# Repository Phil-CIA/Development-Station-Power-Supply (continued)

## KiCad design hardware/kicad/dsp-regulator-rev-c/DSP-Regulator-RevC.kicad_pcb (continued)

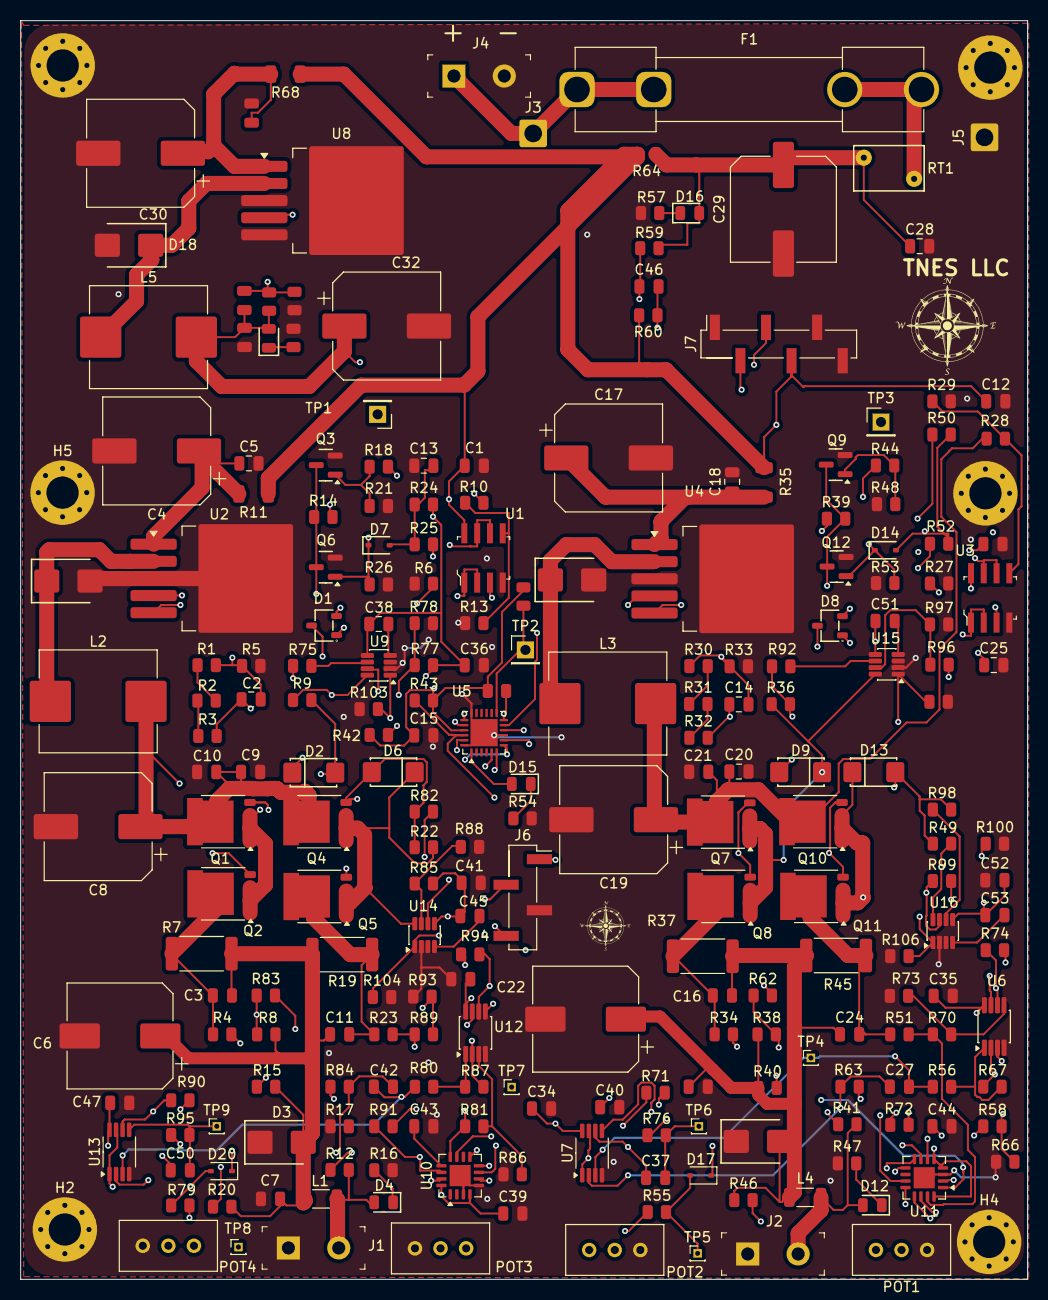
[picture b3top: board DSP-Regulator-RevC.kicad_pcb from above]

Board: 4 copper layers, 100.0 x 125.0 mm, 243 parts (1 on the bottom side), 124 nets.

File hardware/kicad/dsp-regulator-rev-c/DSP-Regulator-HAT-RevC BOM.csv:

"Reference","Qty","Value","LCSC","Manufacturer","Part"
"5mm1","1","","","",""
"10mm1,10mm2","2","","","",""
"C1,C3,C9,C11,C12,C15,C16,C24,C31,C33,C34,C35,C36,C39,C40,C41,C43,C44,C45,C46,C47,C48,C49,C51,C52,C53","26","100nF","C28233,C49678","Samsung Electro-Mechanics,YAGEO","CC0805KRX7R9BB104,CL21B104KCFNNNE"
"C2,C14","2","100pF","C1790","Samsung Electro-Mechanics","CL21C101JBANNNC"
"C4,C30","2","470uf 25V","C48615124","",""
"C5,C18,C20,C38","4","100nF","C28233,C49678","Samsung Electro-Mechanics,YAGEO","CC0805KRX7R9BB104,CL21B104KCFNNNE"
"C6,C22","2","470uf","C48615124","","JVE25V470M10X10"
"C7,C10,C21,C23","4","10uF","C440198","Murata Electronics","GRM21BR61H106KE43L"
"C8,C19,C32","3","330uF 25v","C72510","",""
"C13,C25","2","1nF","C46653","Samsung Electro-Mechanics","CL21B102KBCNNNC"
"C17","1","470uf 50v","C34642","",""
"C26","1","100pF","C1790","Samsung Electro-Mechanics","CL21C101JBANNNC"
"C27,C37,C42,C50","4","1nF","C46653","Samsung Electro-Mechanics","CL21B102KBCNNNC"
"C28","1","100nf","C28233","Samsung Electro-Mechanics","CL21B104KCFNNNE"
"C29","1","1000uf 25v","C401766","","EEEFT1E102UP"
"D1,D8","2","BAT54C,215","C37704","Nexperia","BAT54C,215"
"D2,D6,D9,D13","4","1SMA4742A","C19077480","hongjiacheng","1SMA4742A"
"D3,D11","2","SMBJ6.0CA","C19077561","hongjiacheng","SMBJ6.0CA"
"D4,D12","2","Green","C2297","Hubei KENTO Elec","KT-0805G"
"D5,D10,D18","3","SS54B","C18199181","hongjiacheng","SS54B"
"D7,D14","2","1N5819WS","C191023","Guangdong Hottech","1N5819WS"
"D15,D19","2","Yellow","C2296","Hubei KENTO Elec","KT-0805Y"
"D16","1","Red","C84256","Foshan NationStar Optoelectronics","NCD0805R1"
"D17,D20","2","1N5819WS","C191023","",""
"F1","1","MDL 5","","",""
"J1,J2,J4","3","1935161","","Phoenix Contact",""
"J6","1","1x4 pin 2.54  SMT right","C41417361","",""
"J7","1","1x6 PinHeader","C41417363","",""
"L1,L4","2","L_Ferrite","C85841","",""
"L2,L3,L5","3","33uh","C149598","",""
"POT1,POT2,POT3,POT4","4","3296W-1-103LF","C49190453","Bourns Inc.",""
"Q1,Q2,Q4,Q5,Q7,Q8,Q10,Q11","8","PSMN5R2-60YL","TBD","Nexperia","PSMN5R2-60YLX"
"Q3,Q6,Q9,Q12","4","BSS138","C7420339","hongjiacheng","BSS138"
"R1,R10,R18,R25,R44,R52","6","100Ω","C17408","UNI-ROYAL(Uniroyal Elec)","0805W8F1000T5E"
"R2,R5,R28,R33,R56,R57,R76,R80,R95","9","1kΩ","C17513","UNI-ROYAL(Uniroyal Elec)","0805W8F1001T5E"
"R3","1","1.8kΩ","C17398","UNI-ROYAL(Uniroyal Elec)","0805W8F1801T5E"
"R4,R8,R12,R20,R23,R34,R38,R41,R46,R51,R59,R60,R75,R82,R92,R98","16","10Ω","C17415","UNI-ROYAL(Uniroyal Elec)","0805W8F100JT5E"
"R6,R9,R21,R22,R26,R27,R36,R48,R49,R53,R55,R78,R79,R88,R97,R100","16","100kΩ","C149504","UNI-ROYAL(Uniroyal Elec)","0805W8F1003T5E"
"R7","1","20mΩ","C49164694","",""
"R11,R35,R68","3","0Ω","C17888","UNI-ROYAL(Uniroyal Elec)","1206W4F0000T5E"
"R13,R29","2","33kΩ","C17633","UNI-ROYAL(Uniroyal Elec)","0805W8F3302T5E"
"R14,R39,R42,R43,R58,R62,R63,R70,R71,R72,R81,R83,R84,R89,R90,R91,R101,R102,R103,R104,R105,R106","22","10kΩ","C17414","UNI-ROYAL(Uniroyal Elec)","0805W8F1002T5E"
"R15,R17,R40","3","10Ω","C17415","UNI-ROYAL(Uniroyal Elec)","0805W8F100JT5E"
"R16,R47,R54","3","270Ω","C17590","UNI-ROYAL(Uniroyal Elec)","0805W8F2700T5E"
"R19","1","200mΩ","C7420022","",""
"R24,R50","2","47kΩ","C17713","UNI-ROYAL(Uniroyal Elec)","0805W8F4702T5E"
"R30,R69","2","680Ω","C17798","UNI-ROYAL(Uniroyal Elec)","0805W8F6800T5E"
"R31","1","820Ω","C17837","UNI-ROYAL(Uniroyal Elec)","0805W8F8200T5E"
"R32","1","0Ω","C17477","UNI-ROYAL(Uniroyal Elec)","0805W8F0000T5E"
"R37","1","20m ohms","C49164694","",""
"R45","1","200m ohms","C7420022","",""
"R61","1","3100","C2767486","UNI-ROYAL(Uniroyal Elec)","0805W8F1000T5E"
"R64","1","10mohm","C17477","UNI-ROYAL(Uniroyal Elec)","0805W8F0000T5E"
"R65","1","1k","C17513","UNI-ROYAL(Uniroyal Elec)","0805W8F1001T5E"
"R66,R67,R73,R74,R86,R87,R93,R94","8","510kΩ","C17733","UNI-ROYAL(Uniroyal Elec)","0805W8F5103T5E"
"R77,R85,R96,R99","4","390kΩ","C17656","UNI-ROYAL(Uniroyal Elec)","0805W8F3903T5E"
"RT1","1","5 ohms - 4.5amp","","",""
"TP1,TP2,TP3","3","TestPoint_Small","","",""
"TP4,TP5,TP6,TP7,TP8,TP9","6","TestPoint_Small","","",""
"U1,U3","2","TLV9352","C4366962","Texas Instruments",""
"U2,U4,U8","3","LM2596S-ADJ","C347423","",""
"U5","1","AW9523B","C148077","",""
"U6,U12","2","INA2180A2IDGKR","C2058508","",""
"U7,U13","2","TLV1702AIDGKR","C2870937","",""
"U9,U14,U15,U16","4","LM74502DDFR","C3236215","",""
"U10,U11","2","INA3221","C181255","",""

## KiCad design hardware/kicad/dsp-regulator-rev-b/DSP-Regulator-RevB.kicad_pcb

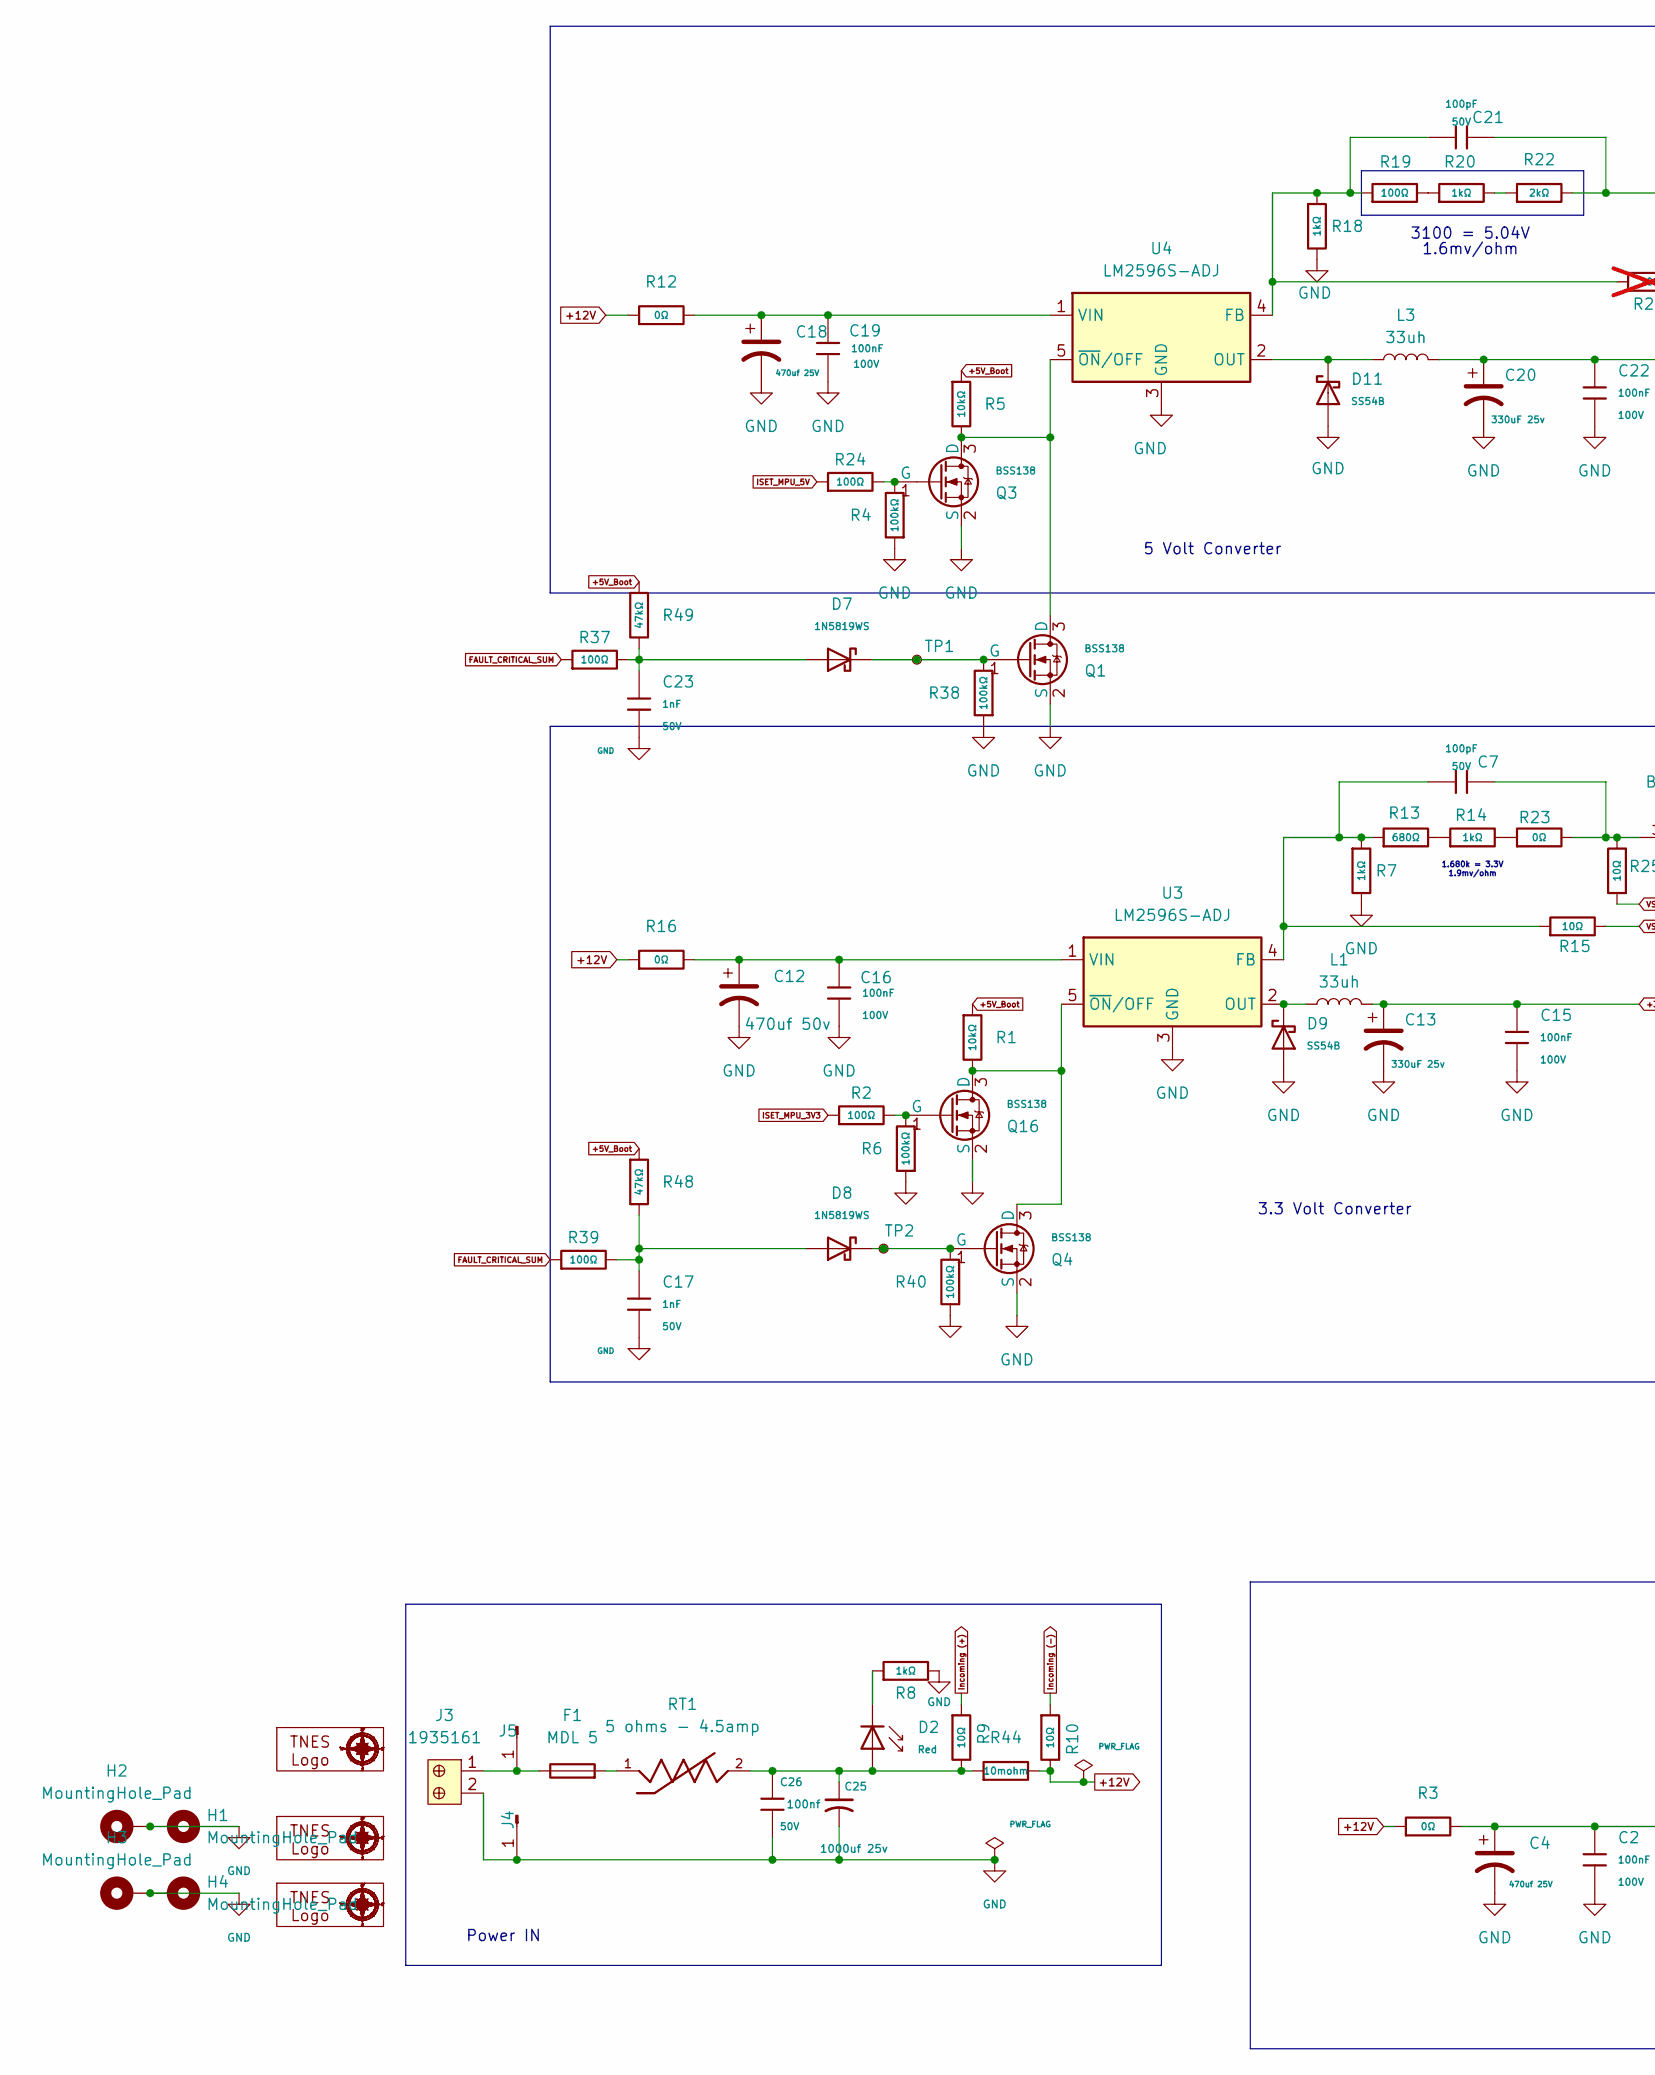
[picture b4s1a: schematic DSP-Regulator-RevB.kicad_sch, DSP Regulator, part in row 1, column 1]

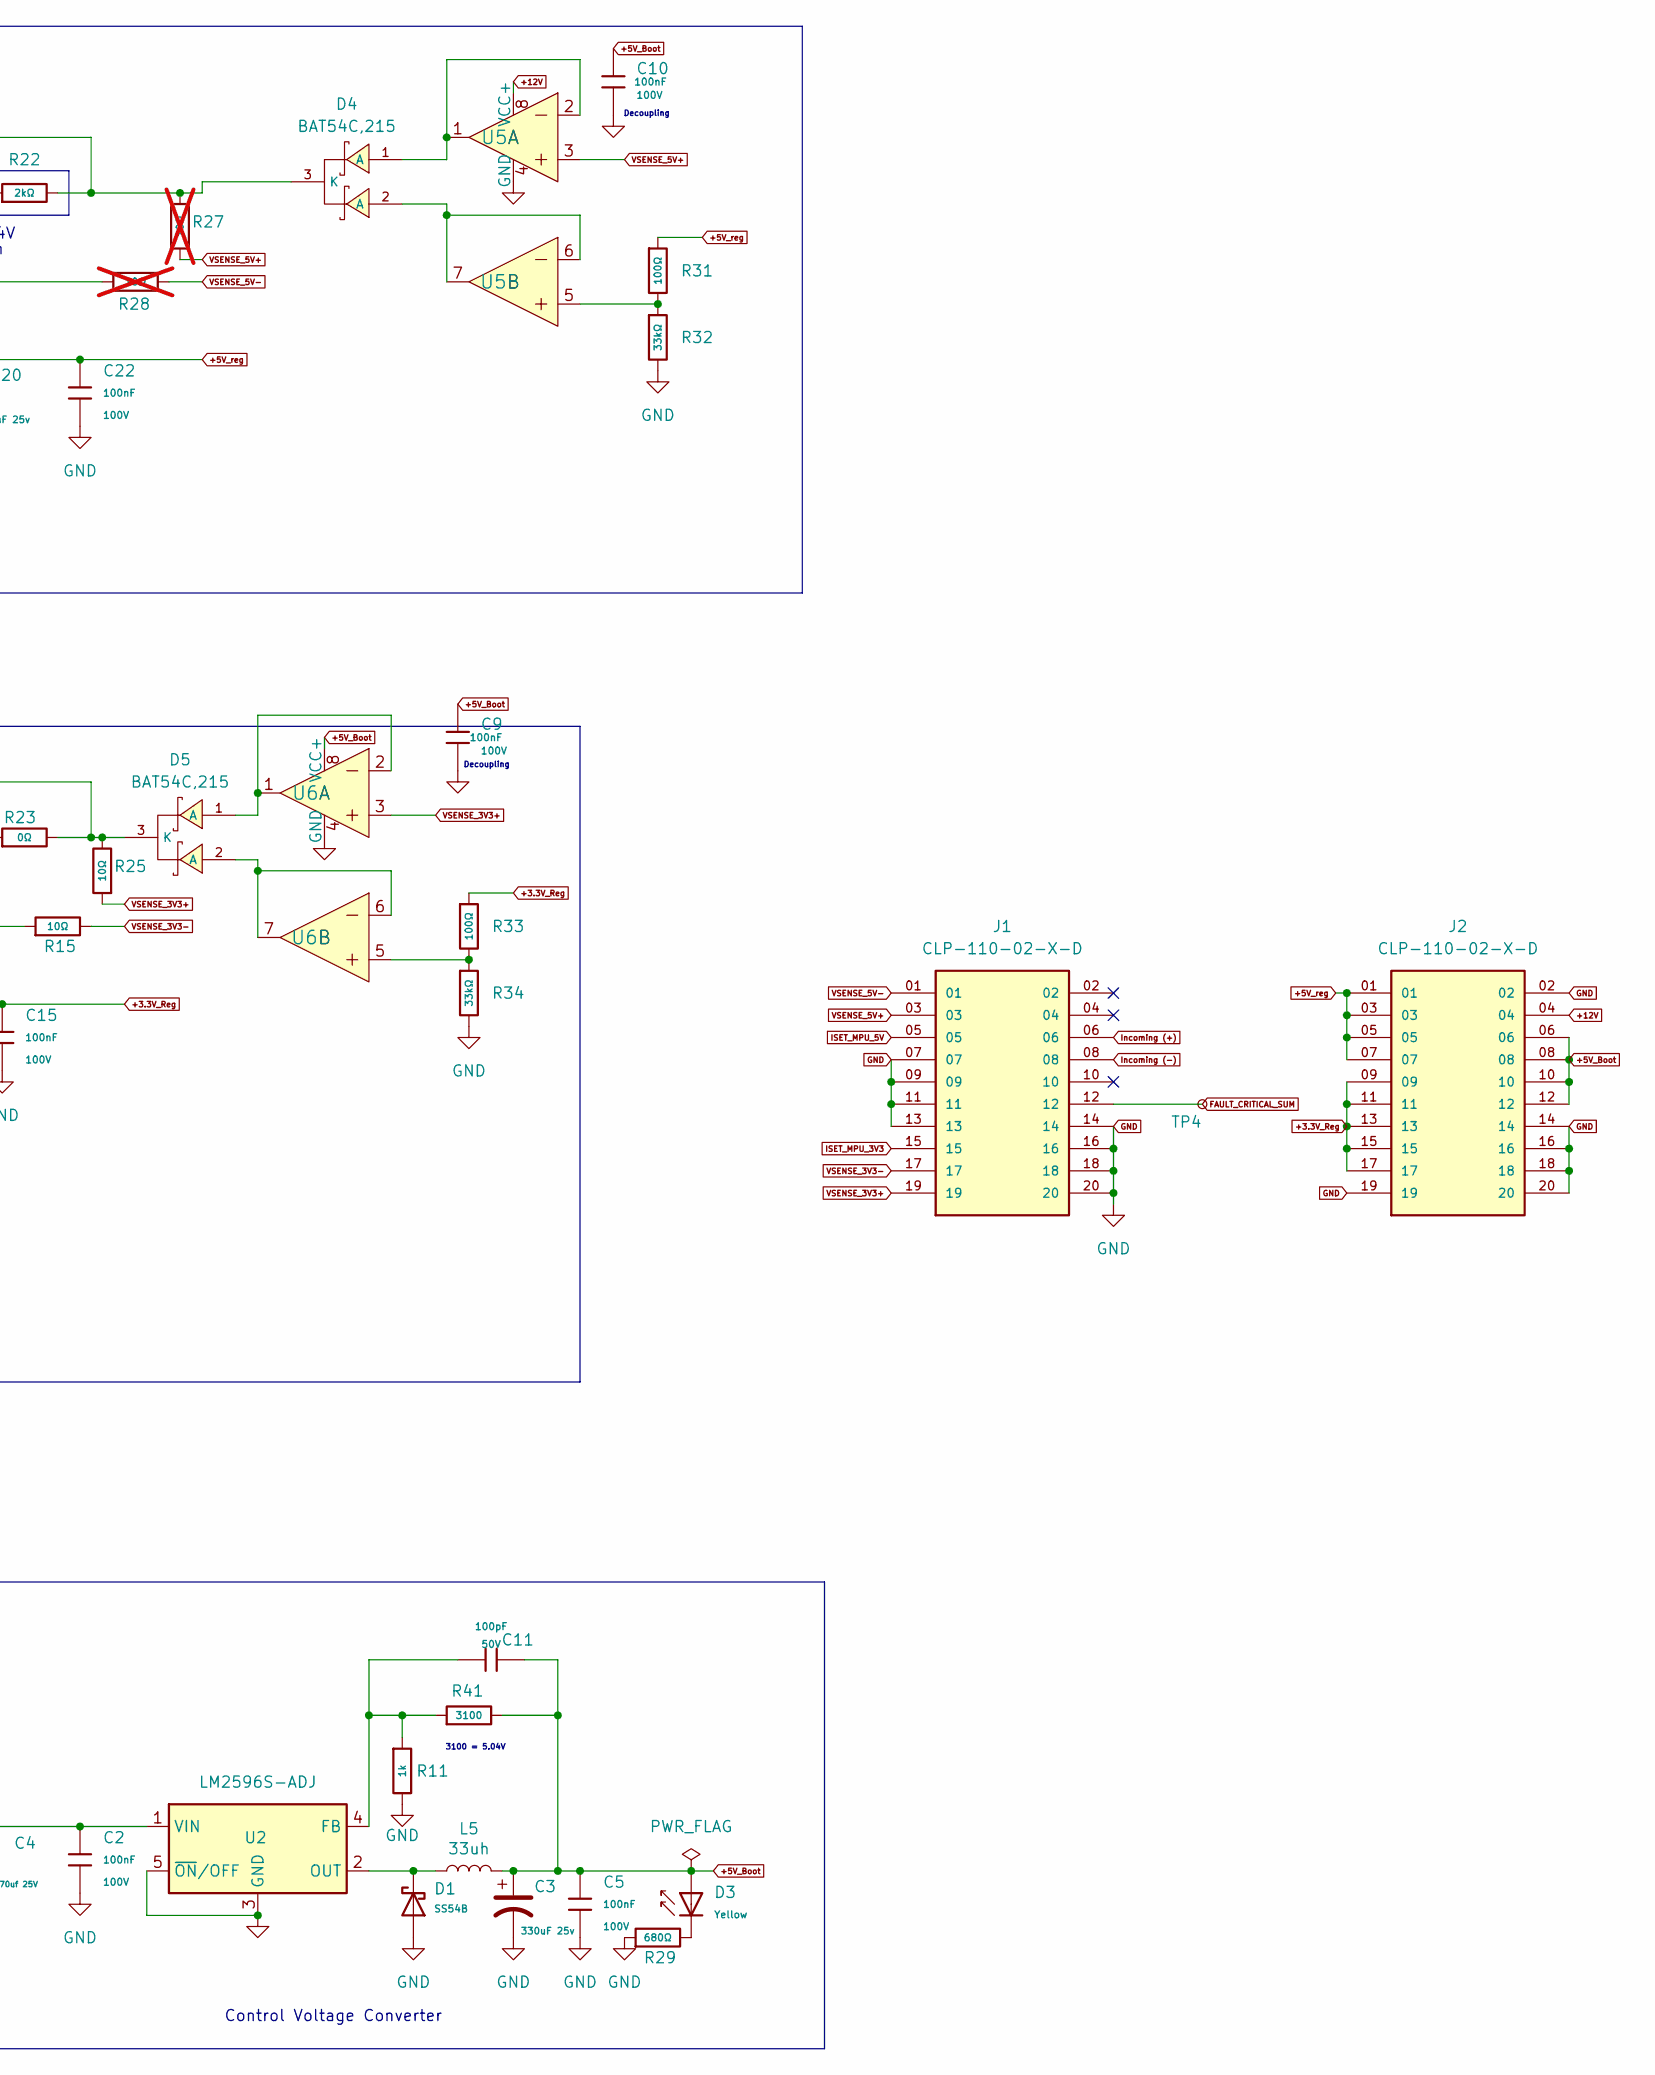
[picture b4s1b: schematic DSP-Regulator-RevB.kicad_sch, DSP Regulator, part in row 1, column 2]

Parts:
5mm1: 5mm LOGO
10mm1, 10mm2: 10mm LOGO
C2, C5, C9, C10, C15, C16, C19, C22: 100nF; C_0805; Voltage Rated 100V; Tolerance ±10%; Part CL21B104KCFNNNE; LCSC C28233
C3, C13, C20: 330uF 25v; CP_Elec_10x10.5; LCSC C72510
C4, C18: 470uf 25V; CP_Elec_10x10.5; Voltage Class 25; LCSC C48615124
C7, C11, C21: 100pF; C_0805; Voltage Rated 50V; Tolerance ±5%; Part CL21C101JBANNNC; LCSC C1790
C12: 470uf 50v; CP_Elec_10x10.5; Voltage Class 50; LCSC C34642
C17, C23: 1nF; C_0805; Voltage Rated 50V; Tolerance ±10%; Part CL21B102KBCNNNC; LCSC C46653
C25: 1000uf 25v; C_Elec_10x10.2; Part EEEFT1E102UP; LCSC C401766
C26: 100nf; C_0805; Voltage Rated 50V; Tolerance ±10%; Part CL21B104KCFNNNE; LCSC C28233
D1, D9, D11: SS54B; D_SMB; Voltage - Forward(Vf@If) 550mV@5.0A; Voltage - DC Reverse(Vr) 40V; Part SS54B; LCSC C18199181
D2: Red; D_0805; Forward Voltage (VF) 1.6V~2.6V; Part NCD0805R1; LCSC C84256
D3: Yellow; D_0805; Part KT-0805Y; LCSC C2296
D4, D5: BAT54C,215; SOT-23-3_L2.9-W1.6-P1.90-LS2.8-BR; Reverse Voltage (Vr) 30V; Forward Voltage (Vf@If) 800mV@100mA; Part BAT54C,215; LCSC C37704
D7, D8: 1N5819WS; D_SOD-323; Forward Voltage (Vf@If) 600mV@1A; Reverse Voltage (Vr) 40V; Part 1N5819WS; LCSC C191023
F1: MDL 5; Fuseholder_Clip-6.3x32mm_Littelfuse_102_Inline_P34.21x7.62m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
H1, H2, H3, H4: MountingHole_Pad; MountingHole_3.2mm_M3_Pad_Via
J1, J2: CLP-110-02-X-D; SAMTEC_CLP-110-02-X-D; PARTREV W
J3: 1935161; Terminal_Block_D1.3mm_P5mm; MPN 1935161; Digi-Key_PN 277-1667-ND
J4, J5: Wire con; SolderWire-1sqmm_1x01_D1.4mm_OD2.7mm
L1, L3, L5: 33uh; L_11.5x10mm_H6mm; LCSC C149598
Q1, Q3, Q4, Q16: BSS138; Q_SOT-23; Part BSS138; LCSC C7420339
R1, R5: 10kΩ; R_0805; Overload Voltage (Max) 150V; Tolerance ±1%; Part 0805W8F1002T5E; LCSC C17414
R2, R19, R24, R31, R33, R37, R39: 100Ω; R_0805; Overload Voltage (Max) 150V; Tolerance ±1%; Part 0805W8F1000T5E; LCSC C17408
R3, R12, R16: 0Ω; R_1206; Overload Voltage (Max) 200V; Tolerance ±1%; Part 1206W4F0000T5E; LCSC C17888
R4, R6, R38, R40: 100kΩ; R_0805; Overload Voltage (Max) 150V; Tolerance ±1%; Part 0805W8F1003T5E; LCSC C149504
R7, R8, R14, R18, R20: 1kΩ; R_0805; Overload Voltage (Max) 150V; Tolerance ±1%; Part 0805W8F1001T5E; LCSC C17513
R9, R10, R15, R25: 10Ω; R_0805; Overload Voltage (Max) 150V; Tolerance ±1%; Part 0805W8F100JT5E; LCSC C17415
R11: 1k; R_0805; Overload Voltage (Max) 150V; Tolerance ±1%; Part 0805W8F1001T5E; LCSC C17513
R13, R29: 680Ω; R_0805; Overload Voltage (Max) 150V; Tolerance ±1%; Part 0805W8F6800T5E; LCSC C17798
R22: 2kΩ; R_0805; Overload Voltage (Max) 150V; Tolerance ±1%; Part 0805W8F2001T5E; LCSC C17604
R23: 0Ω; R_0805; Overload Voltage (Max) 150V; Tolerance ±1%; Part 0805W8F0000T5E; LCSC C17477
R27, R28: 10Ω; R_0805; Overload Voltage (Max) 150V; Tolerance ±1%; Part 0805W8F100JT5E; LCSC C17415; not fitted
R32, R34: 33kΩ; R_0805; Overload Voltage (Max) 150V; Tolerance ±1%; Part 0805W8F3302T5E; LCSC C17633
R41: 3100; R_0805; Overload Voltage (Max) 150V; Tolerance ±1%; Part 0805W8F1000T5E; LCSC C17408
R44: 10mohm; R_0805; Overload Voltage (Max) 150V; Tolerance ±1%; Part 0805W8F0000T5E; LCSC C17477
R48, R49: 47kΩ; R_0805; Overload Voltage (Max) 150V; Tolerance ±1%; Part 0805W8F4702T5E; LCSC C17713
RT1: 5 ohms - 4.5amp; Inrush limiter; PARTREV 8/1/2022
TP1, TP2, TP4: TestPoint_Small; PinHeader_1x01_P2.54mm_Vertical
U2, U3, U4: LM2596S-ADJ; TO-263-5_TabPin3
U5, U6: LMV358IDR; SOIC-8_W3.9mm; MPN LMV358IDR; Digi-Key_PN 296-9571-1-ND

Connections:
+3.3V_Reg: C13.1, C15.1, J2.09, J2.11, J2.13, J2.15, J2.17, L1.2, R33.1
+5V_reg: C20.1, C22.1, J2.01, J2.03, J2.05, J2.07, L3.2, R31.1
FAULT_CRITICAL_SUM: J1.12, R37.1, R39.1, TP4.1
GND: C2.2, C3.2, C4.2, C5.2, C9.2, C10.2, C12.2, C13.2, C15.2, C16.2, C17.2, C18.2, C19.2, C20.2, C22.2, C23.2, C25.2, C26.2, D1.2, D9.2, D11.2, H1.1, H2.1, H3.1, H4.1, J1.07, J1.09, J1.11, J1.13, J1.14, J1.16, J1.18, J1.20, J2.02, J2.14, J2.16, J2.18, J2.19, J2.20, J3.2, J4.1, Q1.2 (S), Q3.2 (S), Q4.2 (S), Q16.2 (S), R4.1, R6.1, R7.2, R8.2, R11.2, R18.2, R29.1, R32.2, R34.2, R38.1, R40.1, U2.3 (GND), U2.5 (~ON/OFF), U3.3 (GND), U4.3 (GND), U5.4 (GND), U6.4 (GND)
ISET_MPU_3V3: J1.15, R2.1
ISET_MPU_5V: J1.05, R24.1
Incoming (+): J1.06, R9.1
Incoming (-): J1.08, R10.1
unnamed: C17.1, D8.2, R39.2, R48.2
unnamed: C23.1, D7.2, R37.2, R49.2
unnamed: C25.1, C26.1, D2.2, R9.2, R44.1, RT1.2
unnamed: D2.1, R8.1
unnamed: D3.1, R29.2
unnamed: D4.1 (A), U5.1, U5.2
unnamed: D4.2 (A), U5.6, U5.7
unnamed: C21.1, D4.3 (K), R22.2, R27.2
unnamed: D5.1 (A), U6.1, U6.2
unnamed: D5.2 (A), U6.6, U6.7
unnamed: C7.1, D5.3 (K), R23.2, R25.2
unnamed: F1.2, RT1.1
unnamed: F1.1, J3.1, J5.1
unnamed: Q1.3 (D), Q3.3 (D), R5.2, U4.5 (~ON/OFF)
unnamed: D7.1, Q1.1 (G), R38.2, TP1.1
unnamed: Q3.1 (G), R4.2, R24.2
unnamed: D8.1, Q4.1 (G), R40.2, TP2.1
unnamed: Q4.3 (D), Q16.3 (D), R1.2, U3.5 (~ON/OFF)
unnamed: Q16.1 (G), R2.2, R6.2
unnamed: R13.2, R14.1
unnamed: R14.2, R23.1
unnamed: R19.2, R20.1
unnamed: R20.2, R22.1
unnamed: R31.2, R32.1, U5.5
unnamed: R33.2, R34.1, U6.5
unnamed: C11.2, R11.1, R41.1, U2.4 (FB)
unnamed: D1.1, L5.1, U2.2 (OUT)
unnamed: C2.1, C4.1, R3.2, U2.1 (VIN)
unnamed: C7.2, R7.1, R13.1, R15.1, U3.4 (FB)
unnamed: D9.1, L1.1, U3.2 (OUT)
unnamed: C12.1, C16.1, R16.2, U3.1 (VIN)
unnamed: C21.2, R18.1, R19.1, R28.2, U4.4 (FB)
unnamed: D11.1, L3.1, U4.2 (OUT)
unnamed: C18.1, C19.1, R12.2, U4.1 (VIN)
VSENSE_3V3+: J1.19, R25.1, U6.3
VSENSE_3V3-: J1.17, R15.2
VSENSE_5V+: J1.03, R27.1, U5.3
VSENSE_5V-: J1.01, R28.1

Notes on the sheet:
Power IN
Control Voltage Converter
3100 = 5.04V
3.3 Volt Converter
5 Volt Converter
1.6mv/ohm
Decoupling
1.680k = 3.3V 1.9mv/ohm

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
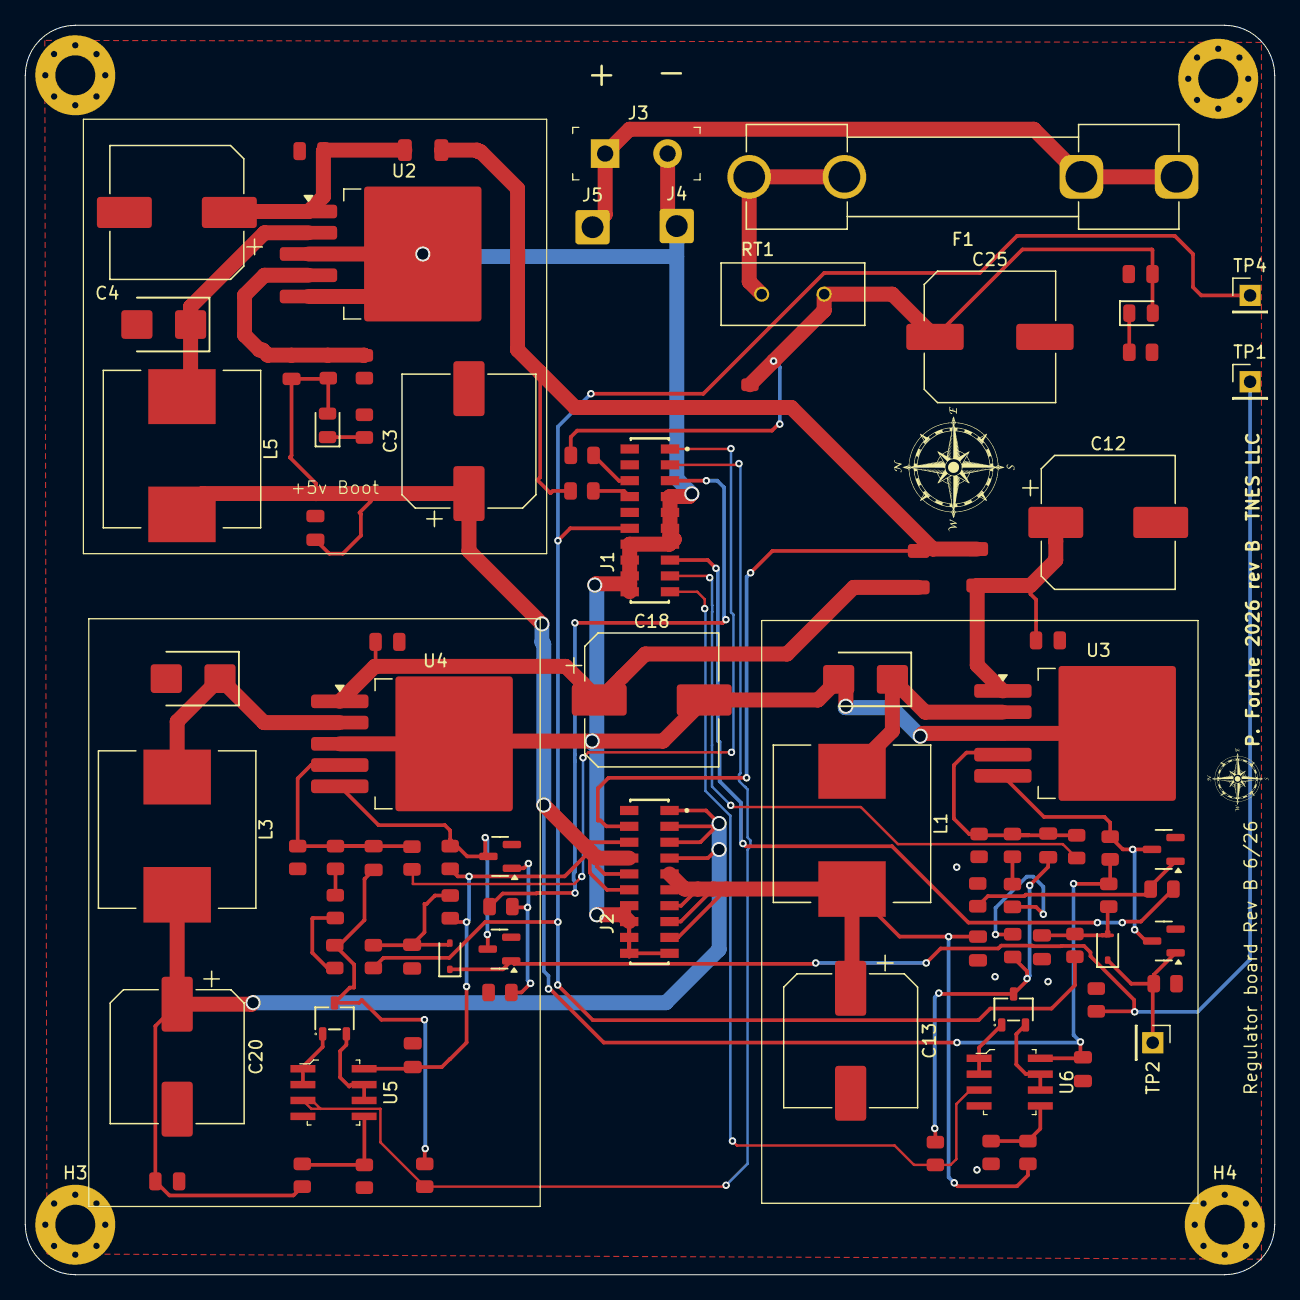
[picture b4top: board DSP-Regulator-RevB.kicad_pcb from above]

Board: 2 copper layers, 100.0 x 100.0 mm, 97 parts (1 on the bottom side), 48 nets.

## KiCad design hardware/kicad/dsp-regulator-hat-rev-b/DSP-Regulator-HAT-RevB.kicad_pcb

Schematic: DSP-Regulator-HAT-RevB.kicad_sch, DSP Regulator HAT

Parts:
5mm1: 5mm LOGO
C1, C2, C20, C21: 10uF; C_0805; Voltage Rated 50V; Tolerance ±10%; Part GRM21BR61H106KE43L; LCSC C440198
C3, C5, C6, C7, C8, C9, C12, C13, C26, C29, C32, C34, C36, C37, C38, C39, C40: 100nF; C_0805; Voltage Rated 50V; Tolerance ±10%; Part CC0805KRX7R9BB104; LCSC C49678
C14, C15, C16, C17: 1nF; C_0805; Voltage Rated 50V; Tolerance ±10%; Part CL21B102KBCNNNC; LCSC C46653
C23, C25: 470uf; CP_Elec_10x10; Part JVE25V470M10X10; LCSC C48615124
C31, C33: C_Small_US; CP_Elec_10x10; Part JVE25V470M10X10; LCSC C48615124
C35: 100uF; C_1206; Voltage Rated 6.3V; Tolerance ±20%; Part CL31A107MQHNNNE; LCSC C15008
D1, D2: SMF05CT1G; SOT-363_L2.0-W1.3-P0.65-LS2.1-BR; Breakdown Voltage (Vbr) 6.2V; Clamping Voltage@Ipp 12.5V; Part SMF05CT1G; LCSC C15879
D3, D4: 1N5819WS; D_SOD-323; LCSC C191023
D5, D8: SMBJ6.0CA; D_SMB; Clamping Voltage 10.3V; Voltage - Breakdown 6.67V; PARTREV F2102; LCSC C19077561
D6: Yellow; D_0805; Part KT-0805Y; LCSC C2296
D7: US1M; D_SMA; LCSC C81191
D9, D11: Green; D_0805; Part KT-0805G; LCSC C2297
D12: WS2812B; LED-SMD_4P-L1.6-W1.5_XL-1615RGBC-WS2812B; LCSC C5349954
D13: USBLC6-2SC6; SOT23-6L; MPN USBLC6-2SC6; Digi-Key_PN 497-5235-1-ND
H1, H2, H3, H4: MountingHole_Pad; MountingHole_3.5mm_Pad_Via
J1, J2: FW-10-05-X-D-XXX-XXX-A; SAMTEC_FW-10-05-X-D-XXX-XXX-A
J3, J12: 20021121-00010C4LF; PinHeader_2x5_P1.27mm; PARTREV S; LCSC C41376037
J4: Fan Control; PinHeader_1x2_P2.5mm_Drill1.1mm; MPN B2B-XH-A(LF)(SN); Digi-Key_PN 455-2247-ND
J5, J6, J7, J8, J16, J17, J18: Conn_01x01_Pin; SolderWire-1sqmm_1x01_D1.4mm_OD2.7mm
J9, J10: 1935161; Terminal_Block_D1.3mm_P5mm; MPN 1935161; Digi-Key_PN 277-1667-ND
J11: USB Hub I2C; JST_B4B-XH-A; PARTREV 7/4/21; LCSC C144394
J13, J19: SWD_Debug_Header; IDC-Header_2x05_P2.54mm_Vertical; LCSC C53207560
J20: Connector, USB-TYPE-C-16P; TYPE-C-SMD_HX-TYPE-C-16PIN; LCSC C2927039
J21: Display Uart; JST_B4B-XH-A; PARTREV 7/4/21; LCSC C144394
L1, L3: L_Ferrite; L_1206_3216Metric; LCSC C85841
POT1, POT2, POT3, POT4: 3296W-1-103LF; Potentiometer_Bourns_3296W_Vertical; MPN TC33X-2-103E; Digi-Key_PN TC33X-103ETR-ND
Q1, Q2, Q3, Q4, Q7, Q8, Q9, Q10: PSMN5R2-60YL; LFPAK56; Part HL3400; LCSC C22469448
Q5: AO3400A; Q_SOT-23; Part AO3400A; LCSC C20917
R1, R2, R3, R4, R10, R51, R53: 100kΩ; R_0805; Overload Voltage (Max) 150V; Tolerance ±1%; Part 0805W8F1003T5E; LCSC C149504
R5, R55, R57: 270Ω; R_0805; Overload Voltage (Max) 150V; Tolerance ±1%; Part 0805W8F2700T5E; LCSC C17590
R7, R8, R11, R12: 100Ω; R_0805; Overload Voltage (Max) 150V; Tolerance ±1%; Part 0805W8F1000T5E; LCSC C17408
R9: 100Ω; R_0805; Overload Voltage (Max) 150V; Tolerance ±1%; Part 0805W8F1000T5E; LCSC Part C105588
R16: 20m ohms; R_2512_6332Metric; LCSC C49164694
R17: 200m ohms; R_2512_6332Metric; LCSC C7420022
R18: 20mΩ; R_2512_6332Metric; LCSC C49164694
R19: 200mΩ; R_2512_6332Metric; LCSC C7420022
R22, R23, R24, R25, R26, R27, R28, R29, R60, R61, R65, R66: 10Ω; R_0805; Overload Voltage (Max) 150V; Tolerance ±1%; Part 0805W8F100JT5E; LCSC C17415
R36, R38, R41, R43: 1kΩ; R_0805; Overload Voltage (Max) 150V; Tolerance ±1%; Part 0805W8F1001T5E; LCSC C17513
R37, R39, R40, R42, R70, R72, R74, R84, R85: 10kΩ; R_0805; Overload Voltage (Max) 150V; Tolerance ±1%; Part 0805W8F1002T5E; LCSC C17414
R48: 56Ω; R_0805; Overload Voltage (Max) 150V; Tolerance ±1%; Part 0805W8F560JT5E; LCSC C17757
R58, R62: 10Ω; R_0805; Overload Voltage (Max) 150V; Tolerance ±1%; Part 0805W8F100JT5E; LCSC C17415; not fitted
R73, R77, R78, R79, R80, R81, R82, R83, R86: 33Ω; R_0805; Overload Voltage (Max) 150V; Tolerance ±1%; Part 0805W8F330JT5E; LCSC C17634
R75, R76: 4.7kΩ; R_0805; Overload Voltage (Max) 150V; Tolerance ±1%; Part 0805W8F4701T5E; LCSC C17673
R87, R88: 5.1kΩ; R_0805; Overload Voltage (Max) 150V; Tolerance ±1%; Part 0805W8F5101T5E; LCSC C27834
TP1, TP2, TP3, TP4, TP7, TP8, TP9, TP13, TP14: TestPoint_Small; PinHeader_1x01_P1.00mm_Vertical
TP2_+5V1, TP11: 5015; KEYSTONE_5015; PARTREV F; LCSC C5199798
TP_+3.3V1: 5015; KEYSTONE_5015; PARTREV F; LCSC C5199798
U1, U2: INA3221; Texas_RGV0016A_VQFN-16-1EP_4x4mm_P0.65mm_EP2.1x2.1mm; LCSC C181255
U3, U4: TLV1704AIPWR; TSSOP-14_4.4x5mm_P0.65mm; LCSC C181596
U5: AHT20_C2757850; Humidity sensor; LCSC Part C2757850
U7: 74HC595D; SOIC-16_L9.9-W3.9-P1.27-LS6.0-BL; Supply Voltage 2V~6V; Part 74HC595D,118; LCSC C5947
U9: AMS1117-3.3; SOT-223-3_TabPin2; LCSC C6186
U10: STM32_BLUE -; STM32 Blue
U11: W25Q128; SOIC-8_L5.3-W5.3-P1.27-LS8.0-BL; Part W25Q128JVSIQ; LCSC C97521
U12: CH340C; SOIC-16_3.9x9.9mm_P1.27mm; LCSC C14267

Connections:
+3.3V Boot: C3.1, C13.1, C29.2, C33.1, C34.1, C35.1, C36.1, C38.2, C39.2, J3.1, J11.1, J12.2, J19.1, R51.1, R53.1, R70.2, R72.1, R74.1, R75.2, R76.2, R84.2, R85.2, TP_+3.3V1.1, U1.4 (VS), U1.16 (VPU), U2.4 (VS), U2.5 (A0), U2.16 (VPU), U5.2 (VDD), U7.16 (VCC), U9.2 (VO), U11.8 (VCC), U12.4 (V3), U12.16 (VCC)
+3.3V_Reg: C1.1, J2.09, J2.11, J2.13, J2.15, J2.17, Q1.1 (S), Q1.2 (S), Q1.3 (S), Q2.1 (S), Q2.2 (S), Q2.3 (S)
+3v3V_Hi_Range: R22.2, U2.12 (IN+1)
+3v3V_low_Range: R25.2, U2.15 (IN+2)
+5V_Boot: C31.1, C32.1, C37.1, D7.1 (K), D12.2 (VDD), J2.06, J2.08, J2.10, J2.12, J4.2, J13.2, J21.1, POT1.1, POT2.1, POT3.1, POT4.1, TP2_+5V1.1, U9.3 (VI), U10.18 (5V)
+5V_Hi_Range: R26.2, U1.12 (IN+1)
+5V_low_Range: R29.2, U1.15 (IN+2)
+5V_reg: C2.1, J2.01, J2.03, J2.05, J2.07, Q3.1 (S), Q3.2 (S), Q3.3 (S), Q4.1 (S), Q4.2 (S), Q4.3 (S)
+12V: J2.04, U3.3 (V+), U4.3 (V+)
-3v3V_Hi_Range: R23.2, U2.11 (IN-1)
-3v3V_low_Range: R24.2, U2.14 (IN-2)
-5V_Hi_Range: R27.2, U1.11 (IN-1)
-5V_low_Range: R28.2, U1.14 (IN-2)
B13: J12.5, U10.2 (B13)
B14: J12.1, U10.3 (B14)
B15: J12.9, U10.4 (B15)
CTS: R77.1, U10.8 (A11), U12.9 (~CTS)
DISP_UART_RX: R79.1, U10.36 (B11)
DISP_UART_TX: R78.1, U10.35 (B10)
ESP- GPIO 3.3V High: R7.2, U7.3 (Q3)
ESP- GPIO 3.3V Low: R8.2, U7.4 (Q4)
ESP- GPIO 5V Hi: R12.2, U7.1 (Q1)
ESP- GPIO 5V Low: R11.2, U7.2 (Q2)
FAULT_CRITICAL_SUM: D3.1 (K), D4.1 (K), R48.1, R72.2, TP7.1, U1.9 (CRITICAL), U2.9 (CRITICAL), U10.28 (A3)
FAULT_WARNING_SUM: R74.2, U1.8 (WARNING), U2.8 (WARNING), U10.33 (B0)
GND: C1.2, C2.2, C3.2, C5.2, C13.2, C20.2, C21.2, C23.2, C25.2, C26.2, C29.1, C31.2, C32.2, C33.2, C34.2, C35.2, C36.2, C37.2, C38.1, C39.1, C40.2, D1.2, D2.2, D5.1, D8.1, D12.3 (GND), D13.2, H1.1, H2.1, H3.1, H4.1, J1.07, J1.09, J1.11, J1.13, J1.14, J1.16, J1.18, J1.20, J2.02, J2.14, J2.16, J2.18, J2.19, J2.20, J3.2, J3.10, J6.1, J8.1, J9.1, J10.1, J11.4, J12.4, J13.1, J13.7, J16.1, J17.1, J18.1, J19.3, J19.5, J19.9, J20.A12B1 (GND), J20.B12A1 (GND), J20.S1 (SHIELD), J21.2, POT1.3, POT2.3, POT3.3, POT4.3, Q5.2 (S), R1.2, R2.2, R3.2, R4.2, R5.2, R10.2, R55.2, R57.2, R61.1, R66.1, R87.2, R88.2, TP11.1, U1.3 (GND), U1.5 (A0), U2.3 (GND), U3.8 (-IN3), U3.9 (+IN3), U3.10 (-IN4), U3.11 (+IN4), U3.12 (V-), U4.8 (-IN3), U4.9 (+IN3), U4.10 (-IN4), U4.11 (+IN4), U4.12 (V-), U5.5 (GND), U7.8 (GND), U7.13 (OE#), U9.1 (GND), U10.19 (G), U10.39 (GND), U10.40 (GND), U10.44 (GND), U11.4 (GND), U12.1 (GND)
ISET_MPU_3V3: J1.15, U7.5 (Q5), U10.26 (A1)
ISET_MPU_5V: J1.05, U7.15 (Q0), U10.25 (A0)
Incoming (+): C12.1, D2.6, J1.06, U2.2 (IN+3)
Incoming (-): C12.2, D2.5, J1.08, U2.1 (IN-3)
I²C SCL_0: J3.5, J11.2, R75.1, U1.6 (SCL), U2.6 (SCL), U5.3 (SCL), U10.16 (B8)
I²C SDA_0: J3.6, J11.3, R76.1, U1.7 (SDA), U2.7 (SDA), U5.4 (SDA), U10.17 (B9)
Memory_CS: U10.5 (A8), U11.1 (CS#)
NRST: J3.9, J19.10, U10.37 (R)
unnamed: C6.2, Q10.1 (S), Q10.2 (S), Q10.3 (S), R19.1, R29.1, R43.1
unnamed: C7.1, Q7.1 (S), Q7.2 (S), Q7.3 (S), R16.1, R22.1, R36.2
unnamed: C8.2, Q8.1 (S), Q8.2 (S), Q8.3 (S), R17.1, R25.1, R41.1
unnamed: C9.1, Q9.1 (S), Q9.2 (S), Q9.3 (S), R18.1, R26.1, R38.2
unnamed: C7.2, C8.1, C20.1, C23.1, D5.2, L1.1, R16.2, R17.2, R23.1, R24.1, R58.1
unnamed: D3.2 (A), R51.2, TP9.1, U4.1 (OUT2), U4.2 (OUT1)
unnamed: D4.2 (A), R53.2, TP8.1, U3.1 (OUT2), U3.2 (OUT1)
unnamed: D6.1, R5.1
unnamed: D7.2 (A), J4.1, Q5.3 (D)
unnamed: D9.1, R55.1
unnamed: D11.1, R57.1
unnamed: D13.4, J20.A7 (D-), J20.B7 (D-)
unnamed: D13.6, J20.A6 (D+), J20.B6 (D+)
unnamed: J1.12, R48.2
unnamed: J13.3, R73.2
unnamed: J13.4, R80.1
unnamed: J13.5, R77.2
unnamed: J13.6, R81.1
unnamed: J13.8, R82.1
unnamed: J13.9, R86.2
unnamed: J13.10, R83.1
unnamed: J20.A5 (CC1), R88.1
unnamed: J20.B5 (CC2), R87.1
unnamed: J20.A8 (SBU1), J20.B8 (SBU2)
unnamed: J21.3, R78.2
unnamed: J21.4, R79.2
unnamed: POT1.2, R37.1
unnamed: POT2.2, R40.1
unnamed: POT3.2, R42.1
unnamed: POT4.2, R39.1
unnamed: Q1.5 (D), Q7.5 (D)
unnamed: Q1.4 (G), Q7.4 (G), R1.1, R7.1
unnamed: Q2.5 (D), Q8.5 (D)
unnamed: Q2.4 (G), Q8.4 (G), R2.1, R8.1
unnamed: Q3.5 (D), Q9.5 (D)
unnamed: Q3.4 (G), Q9.4 (G), R3.1, R11.1
unnamed: Q5.1 (G), R9.2, R10.1
unnamed: Q4.5 (D), Q10.5 (D)
unnamed: Q4.4 (G), Q10.4 (G), R4.1, R12.1
unnamed: C5.1, U1.13 (TC)
unnamed: C26.1, U2.13 (TC)
unnamed: C14.2, R36.1, TP1.1, U3.5 (+IN1)
unnamed: C14.1, R37.2, U3.4 (-IN1)
unnamed: C16.2, R41.2, TP4.1, U3.7 (+IN2)
unnamed: C16.1, R40.2, U3.6 (-IN2)
unnamed: C15.2, R38.1, TP2.1, U4.5 (+IN1)
unnamed: C15.1, R39.2, U4.4 (-IN1)
unnamed: C17.2, R43.2, TP3.1, U4.7 (+IN2)
unnamed: C17.1, R42.2, U4.6 (-IN2)
unnamed: R70.1, U7.10 (MR#)
unnamed: D6.2, U7.7 (Q7)
unnamed: R85.1, U11.3 (IO2)
unnamed: R84.1, U11.7 (IO3)
unnamed: D13.1, U12.5 (UD+)
unnamed: D13.3, U12.6 (UD-)
PB5: J12.6, R9.1, U10.13 (B5)
PB6: J12.10, U10.14 (B6)
PB7: R86.1, U10.15 (B7)
RTS: R73.1, U10.9 (A12), U12.14 (~RTS)
SPI SCK: R80.2, U7.11 (SHCP), U10.30 (A5), U11.6 (CLK)
SPI_CS: R83.2, U10.1 (B12)
SPI_MISO: R81.2, U10.31 (A6), U11.2 (DO)
SPI_MOSI: R82.2, U7.14 (DS), U10.32 (A7), U11.5 (DI)
SR_Latch: U7.12 (STCP), U10.29 (A4)
SWDCLK: J3.8, J19.4, TP13.1, U10.43 (SWCLK)
SWDIO: J3.7, J19.2, TP14.1, U10.42 (SW0)
Shunt -: C6.1, C9.2, C21.1, C25.1, D8.2, L3.1, R18.2, R19.2, R27.1, R28.1, R62.1
Status_LED: D12.4 (DIN), U10.22 (C13)
UART1_RX: J3.4, U10.7 (A10), U12.2 (TXD)
UART1_TX: J3.3, U10.6 (A9), U12.3 (RXD)
VBUS: C40.1, D13.5, J20.A9B4 (VBUS), J20.B9A4 (VBUS)
VSENSE_3V3+: D1.6, J1.19, R58.2, R60.2
VSENSE_3V3-: D1.5, J1.17, R61.2
VSENSE_5V+: D1.3, J1.03, R62.2, R65.2
VSENSE_5V-: D1.1, J1.01, R66.2
V_out +3V3: D9.2, J7.1, J9.2, L1.2, R60.1
V_out +5V: D11.2, J5.1, J10.2, L3.2, R65.1

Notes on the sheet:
Spare Units
Logic analyzer connector
FW-10-05-L-D-400-150-A Samtec
Inter connect
Channel 1 5 volts
Connectors
Voltage Measuring
I2C Pull-Ups
Channel 2 3.3 volts
Temp sensor
3.3v control
16M Memory
Spare Outputs
Regulator control outputs
